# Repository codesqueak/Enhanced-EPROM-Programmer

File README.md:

# Enhanced EPROM-Programmer Version 2.7

2708 / 2716 Enhanced EPROM Programmer

## Introduction

This card has been designed to be a functional replacement for the Bits & PCs Nascom EPROM Programmer.  It is fully compatible with the existing software.

The card is a completely new implementation of the design with a number of improvements over the original:

* Single power source requirement (+5V only)
* Completely new track layout
* All components are readily available from commercial component suppliers (..and eBay!)
* Single power switch,  EPROM selection via standard 12 PIN DIL socket mounted switch
* LED power indicator
* Power test points
* Adjustable 25V feed for 2708's

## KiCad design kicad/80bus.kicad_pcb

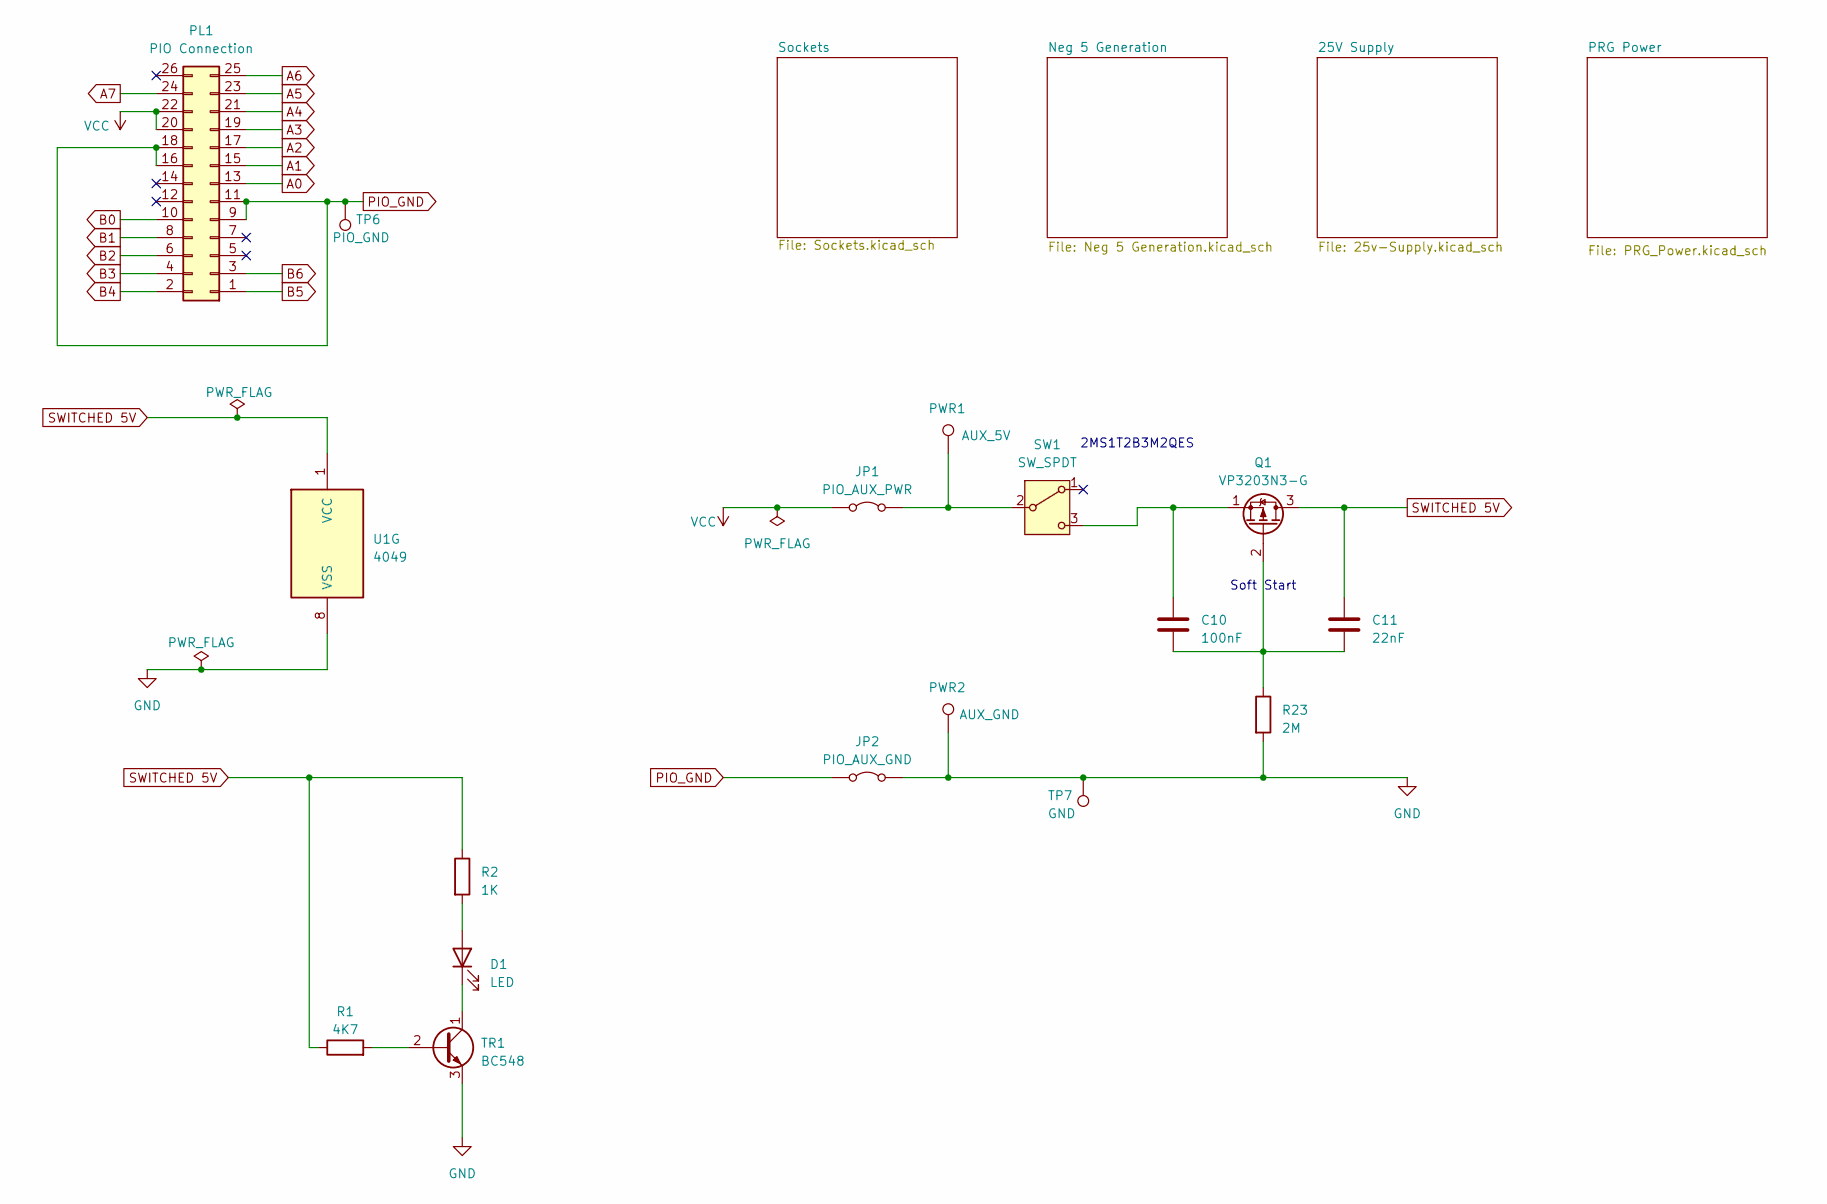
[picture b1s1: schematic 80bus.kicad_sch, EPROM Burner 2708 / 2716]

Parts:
C10: 100nF; C_Disc_D5.0mm_W2.5mm_P5.00mm
C11: 22nF; C_Disc_D5.0mm_W2.5mm_P5.00mm
D1: LED; LED_D3.0mm
JP1: PIO_AUX_PWR; PinHeader_1x02_P2.54mm_Vertical
JP2: PIO_AUX_GND; PinHeader_1x02_P2.54mm_Vertical
PL1: PIO Connection; PinHeader_2x13_P2.54mm_Vertical
PWR1: AUX_5V; TestPoint_THTPad_4.0x4.0mm_Drill2.0mm
PWR2: AUX_GND; TestPoint_THTPad_4.0x4.0mm_Drill2.0mm
Q1: VP3203N3-G; TO-92L_Inline
R1: 4K7; R_Axial_DIN0309_L9.0mm_D3.2mm_P12.70mm_Horizontal
R2: 1K; R_Axial_DIN0309_L9.0mm_D3.2mm_P12.70mm_Horizontal
R23: 2M; R_Axial_DIN0309_L9.0mm_D3.2mm_P12.70mm_Horizontal
SW1: SW_SPDT; PinHeader_1x03_P2.54mm_Vertical
TP6: PIO_GND; TestPoint_THTPad_2.0x2.0mm_Drill1.0mm
TP7: GND; TestPoint_THTPad_2.0x2.0mm_Drill1.0mm
TR1: BC548; TO-92_Inline_Wide
U1: 4049; DIP-16_W7.62mm_Socket

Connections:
A0: PL1.13; also elsewhere on the board
A1: PL1.15; also elsewhere on the board
A2: PL1.17; also elsewhere on the board
A3: PL1.19; also elsewhere on the board
A4: PL1.21; also elsewhere on the board
A5: PL1.23; also elsewhere on the board
A6: PL1.25; also elsewhere on the board
A7: PL1.24; also elsewhere on the board
B0: PL1.10; also elsewhere on the board
B1: PL1.8; also elsewhere on the board
B2: PL1.6; also elsewhere on the board
B3: PL1.4; also elsewhere on the board
B4: PL1.2; also elsewhere on the board
B5: PL1.1; also elsewhere on the board
B6: PL1.3; also elsewhere on the board
GND: JP2.1 (A), PWR2.1, R23.2, TP7.1, TR1.3 (E), U1.8 (VSS); also elsewhere on the board
unnamed: D1.2 (A), R2.2
unnamed: D1.1 (K), TR1.1 (C)
unnamed: JP1.1 (A), PWR1.1, SW1.2 (B)
unnamed: C10.2, C11.2, Q1.2 (G), R23.1
unnamed: C10.1, Q1.1 (S), SW1.3 (C)
unnamed: R1.2, TR1.2 (B)
PIO_GND: JP2.2 (B), PL1.9, PL1.11, PL1.16, PL1.18, TP6.1
SWITCHED 5V: C11.1, Q1.3 (D), R1.1, R2.1, U1.1 (VCC); also elsewhere on the board
VCC: JP1.2 (B), PL1.20, PL1.22

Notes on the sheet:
Soft Start
2MS1T2B3M2QES

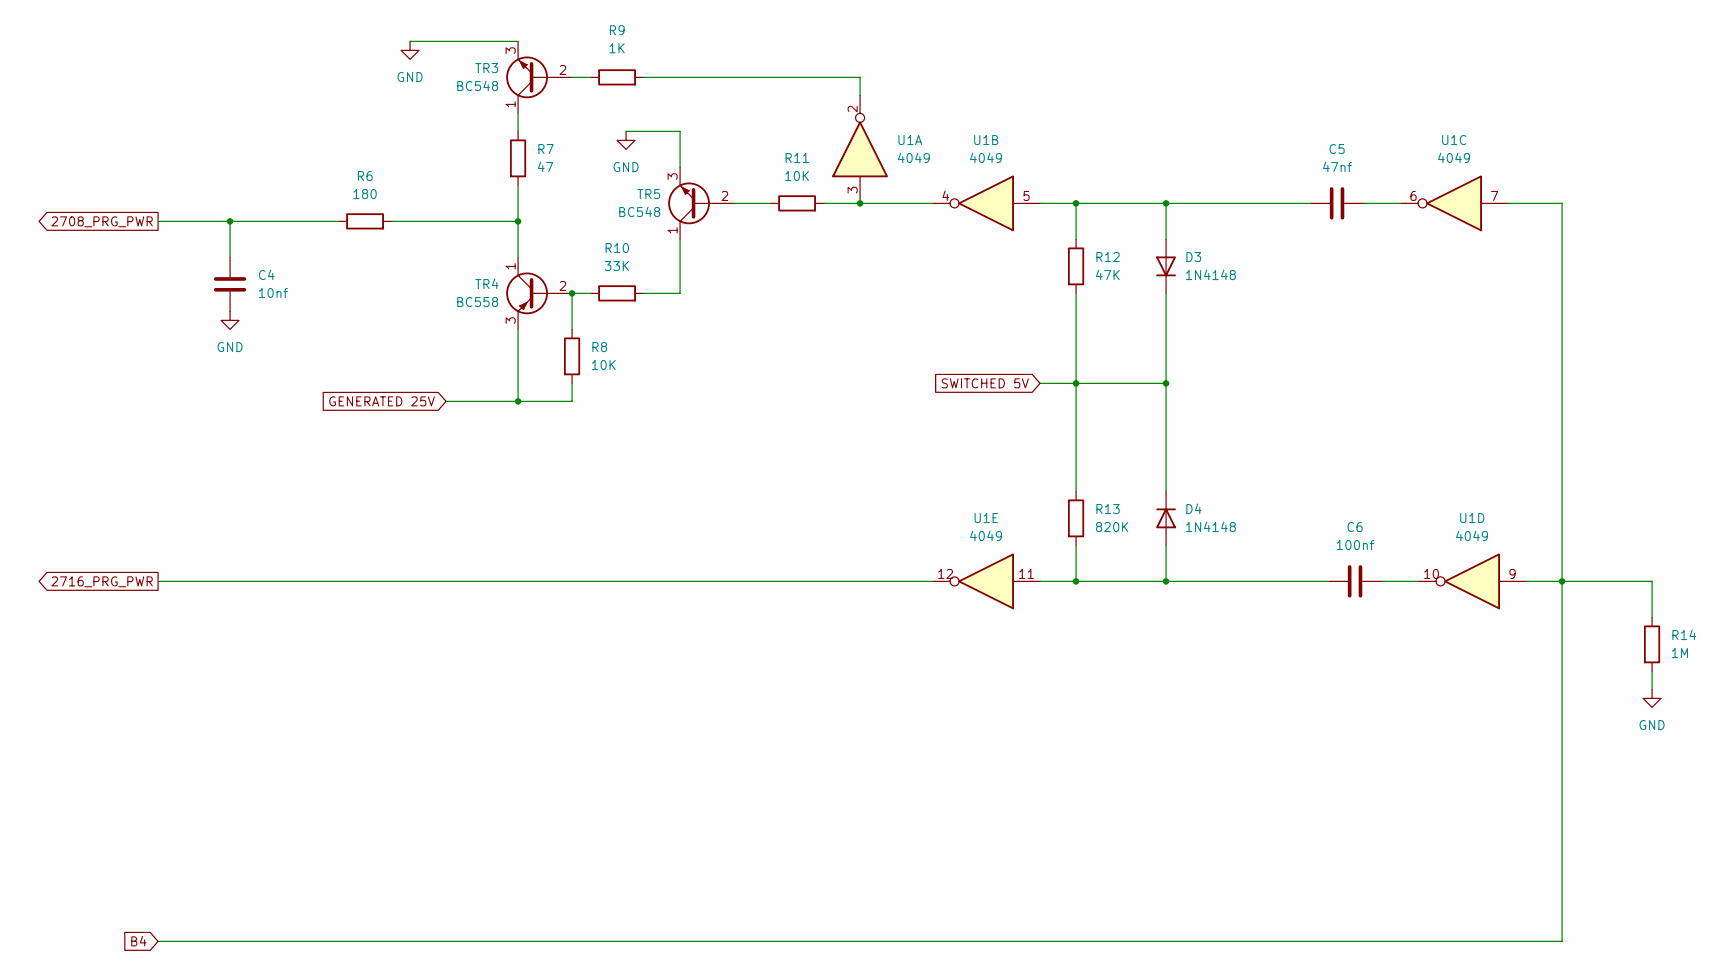
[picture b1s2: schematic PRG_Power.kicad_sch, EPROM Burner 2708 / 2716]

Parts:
C4: 10nf; C_Disc_D5.0mm_W2.5mm_P5.00mm
C5: 47nf; C_Disc_D5.0mm_W2.5mm_P5.00mm
C6: 100nf; C_Disc_D5.0mm_W2.5mm_P5.00mm
D3, D4: 1N4148; D_DO-41_SOD81_P10.16mm_Horizontal
R6: 180; R_Axial_DIN0309_L9.0mm_D3.2mm_P12.70mm_Horizontal
R7: 47; R_Axial_DIN0309_L9.0mm_D3.2mm_P12.70mm_Horizontal
R8, R11: 10K; R_Axial_DIN0309_L9.0mm_D3.2mm_P12.70mm_Horizontal
R9: 1K; R_Axial_DIN0309_L9.0mm_D3.2mm_P12.70mm_Horizontal
R10: 33K; R_Axial_DIN0309_L9.0mm_D3.2mm_P12.70mm_Horizontal
R12: 47K; R_Axial_DIN0309_L9.0mm_D3.2mm_P12.70mm_Horizontal
R13: 820K; R_Axial_DIN0309_L9.0mm_D3.2mm_P12.70mm_Horizontal
R14: 1M; R_Axial_DIN0309_L9.0mm_D3.2mm_P12.70mm_Horizontal
TR3, TR5: BC548; TO-92_Inline_Wide
TR4: BC558; TO-92_Inline_Wide
U1: 4049; DIP-16_W7.62mm_Socket

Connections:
2708_PRG_PWR: C4.1, R6.1; also elsewhere on the board
2716_PRG_PWR: U1.12; also elsewhere on the board
B4: R14.1, U1.7, U1.9; also elsewhere on the board
GENERATED 25V: R8.2, TR4.3 (E); also elsewhere on the board
GND: C4.2, R14.2, TR3.3 (E), TR5.3 (E); also elsewhere on the board
unnamed: C5.2, U1.6
unnamed: C6.1, U1.10
unnamed: C5.1, D3.2 (A), R12.1, U1.5
unnamed: C6.2, D4.2 (A), R13.2, U1.11
unnamed: R9.2, U1.2
unnamed: R11.2, U1.3, U1.4
unnamed: R9.1, TR3.2 (B)
unnamed: R7.1, TR3.1 (C)
unnamed: R8.1, R10.1, TR4.2 (B)
unnamed: R6.2, R7.2, TR4.1 (C)
unnamed: R11.1, TR5.2 (B)
unnamed: R10.2, TR5.1 (C)
SWITCHED 5V: D3.1 (K), D4.1 (K), R12.2, R13.1; also elsewhere on the board

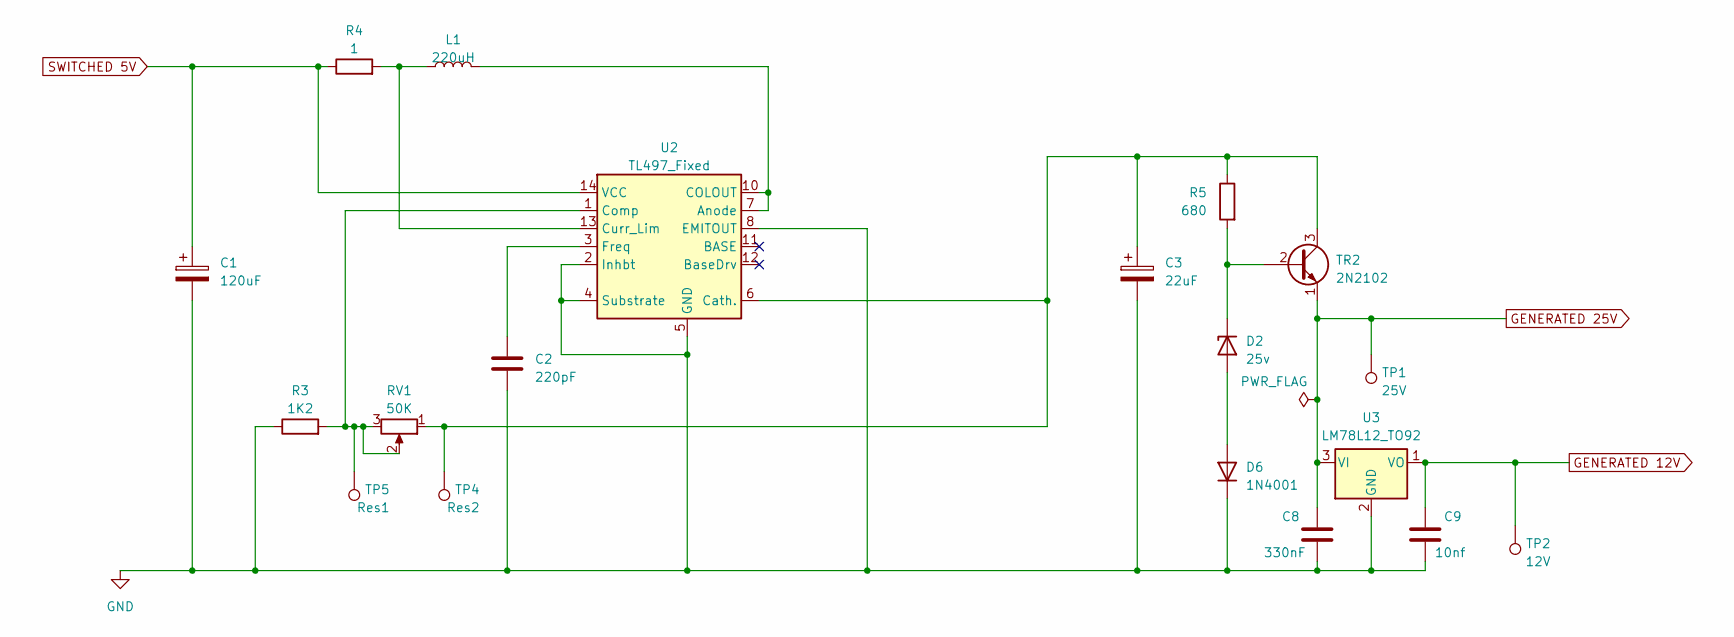
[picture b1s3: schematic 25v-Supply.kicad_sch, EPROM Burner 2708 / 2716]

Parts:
C1: 120uF; CP_Radial_D10.0mm_P5.00mm
C2: 220pF; C_Disc_D5.0mm_W2.5mm_P5.00mm
C3: 22uF; CP_Radial_D5.0mm_P2.50mm
C8: 330nF; C_Disc_D5.0mm_W2.5mm_P5.00mm
C9: 10nf; C_Disc_D5.0mm_W2.5mm_P5.00mm
D2: 25v; D_DO-41_SOD81_P12.70mm_Horizontal
D6: 1N4001; D_DO-41_SOD81_P10.16mm_Horizontal
L1: 220uH; L_Radial_D7.8mm_P5.00mm_Fastron_07HCP
R3: 1K2; R_Axial_DIN0309_L9.0mm_D3.2mm_P12.70mm_Horizontal
R4: 1; R_Axial_DIN0309_L9.0mm_D3.2mm_P12.70mm_Horizontal
R5: 680; R_Axial_DIN0309_L9.0mm_D3.2mm_P12.70mm_Horizontal
RV1: 50K; Potentiometer_Vishay_43_Horizontal
TP1: 25V; TestPoint_THTPad_2.0x2.0mm_Drill1.0mm
TP2: 12V; TestPoint_THTPad_2.0x2.0mm_Drill1.0mm
TP4: Res2; TestPoint_THTPad_2.0x2.0mm_Drill1.0mm
TP5: Res1; TestPoint_THTPad_2.0x2.0mm_Drill1.0mm
TR2: 2N2102; TO-39-3
U2: TL497_Fixed; DIP-14_W7.62mm_Socket
U3: LM78L12_TO92; TO-92_Inline

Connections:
GENERATED 12V: C9.1, TP2.1, U3.1 (VO); also elsewhere on the board
GENERATED 25V: C8.1, TP1.1, TR2.1 (E), U3.3 (VI); also elsewhere on the board
GND: C1.2, C2.2, C3.2, C8.2, C9.2, D6.1 (K), R3.1, U2.2 (Inhbt), U2.4 (Substrate), U2.5 (GND), U2.8 (EMITOUT), U3.2 (GND); also elsewhere on the board
unnamed: D2.2 (A), D6.2 (A)
unnamed: D2.1 (K), R5.2, TR2.2 (B)
unnamed: C3.1, R5.1, RV1.1, TP4.1, TR2.3 (C), U2.6 (Cath.)
unnamed: L1.2, U2.7 (Anode), U2.10 (COLOUT)
unnamed: R3.2, RV1.2, RV1.3, TP5.1, U2.1 (Comp)
unnamed: L1.1, R4.2, U2.13 (Curr_Lim)
unnamed: C2.1, U2.3 (Freq)
SWITCHED 5V: C1.1, R4.1, U2.14 (VCC); also elsewhere on the board

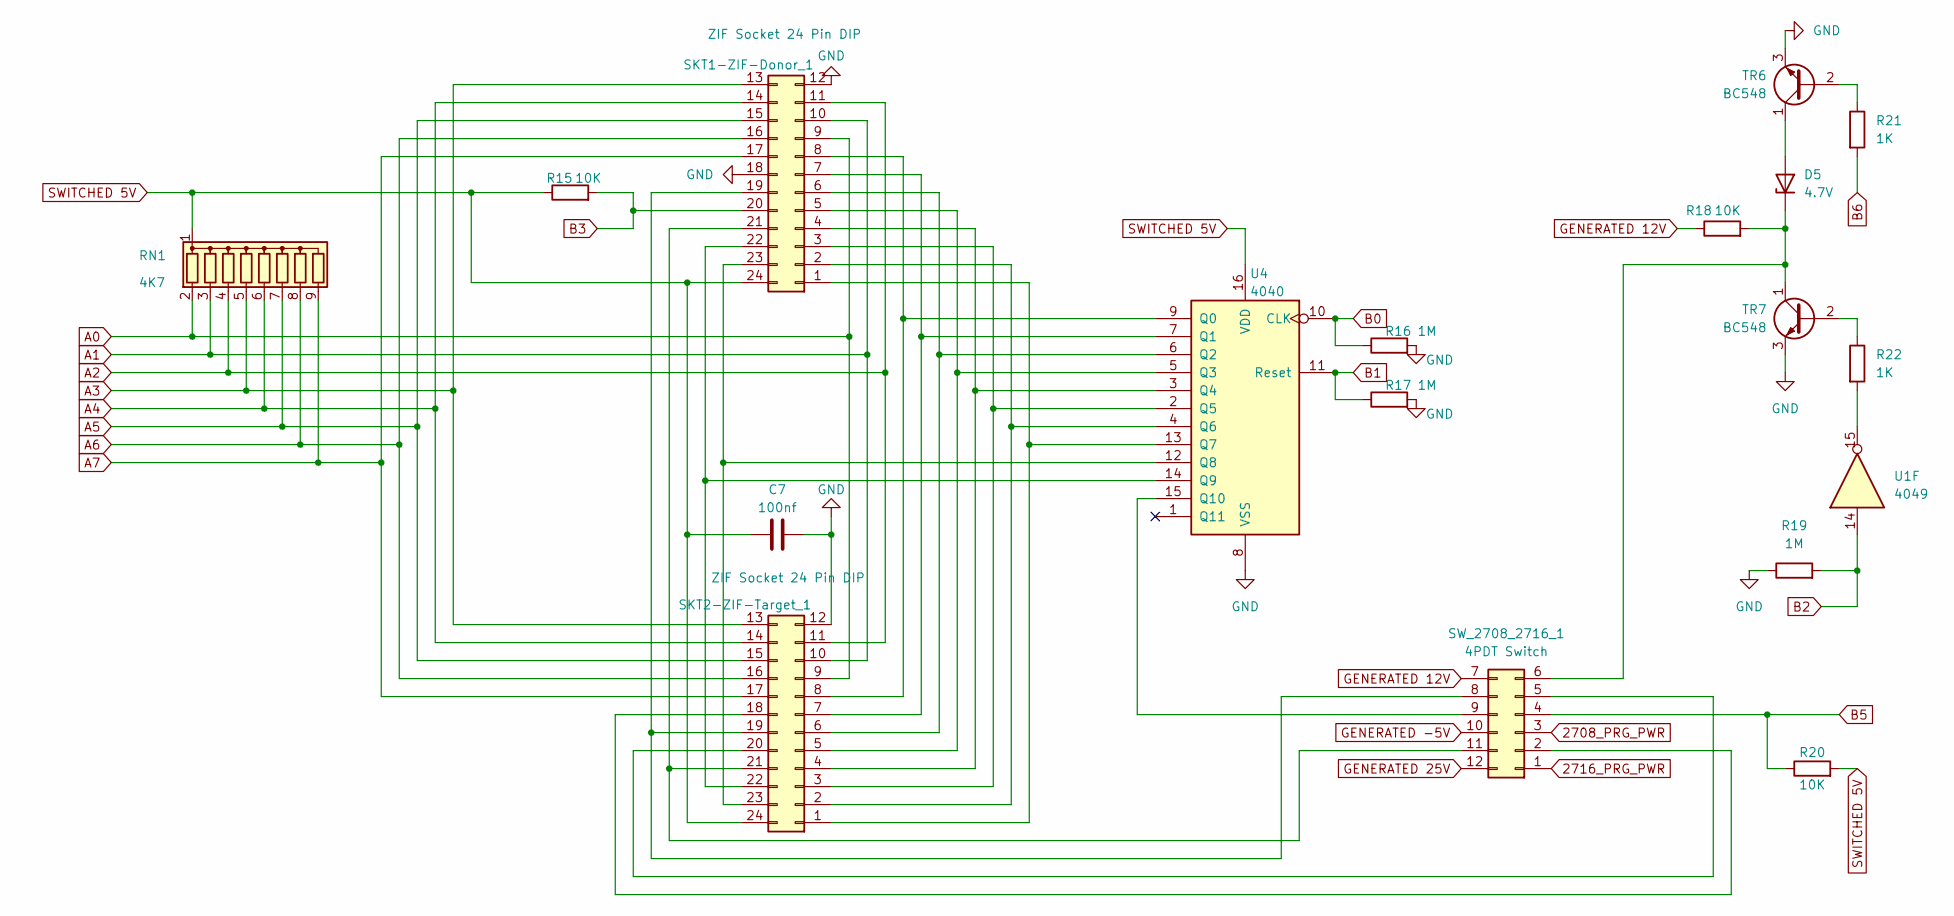
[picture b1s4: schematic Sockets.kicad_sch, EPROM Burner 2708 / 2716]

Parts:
C7: 100nf; C_Disc_D5.0mm_W2.5mm_P5.00mm
D5: 4.7V; D_DO-41_SOD81_P12.70mm_Horizontal
R15, R18, R20: 10K; R_Axial_DIN0309_L9.0mm_D3.2mm_P12.70mm_Horizontal
R16, R17, R19: 1M; R_Axial_DIN0309_L9.0mm_D3.2mm_P12.70mm_Horizontal
R21, R22: 1K; R_Axial_DIN0309_L9.0mm_D3.2mm_P12.70mm_Horizontal
RN1: 4K7; R_Array_SIP9
SKT1-ZIF-Donor_1, SKT2-ZIF-Target_1: ZIF Socket 24 Pin DIP; DIP-24_W15.24mm_Socket
SW_2708_2716_1: 4PDT Switch; DIP-12_W7.62mm_Socket
TR6, TR7: BC548; TO-92_Inline_Wide
U1: 4049; DIP-16_W7.62mm_Socket
U4: 4040; DIP-16_W7.62mm_Socket

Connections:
2708_PRG_PWR: SW_2708_2716_1.3; also elsewhere on the board
2716_PRG_PWR: SW_2708_2716_1.1; also elsewhere on the board
A0: RN1.2 (R1), SKT1-ZIF-Donor_1.9, SKT2-ZIF-Target_1.9; also elsewhere on the board
A1: RN1.3 (R2), SKT1-ZIF-Donor_1.10, SKT2-ZIF-Target_1.10; also elsewhere on the board
A2: RN1.4 (R3), SKT1-ZIF-Donor_1.11, SKT2-ZIF-Target_1.11; also elsewhere on the board
A3: RN1.5 (R4), SKT1-ZIF-Donor_1.13, SKT2-ZIF-Target_1.13; also elsewhere on the board
A4: RN1.6 (R5), SKT1-ZIF-Donor_1.14, SKT2-ZIF-Target_1.14; also elsewhere on the board
A5: RN1.7 (R6), SKT1-ZIF-Donor_1.15, SKT2-ZIF-Target_1.15; also elsewhere on the board
A6: RN1.8 (R7), SKT1-ZIF-Donor_1.16, SKT2-ZIF-Target_1.16; also elsewhere on the board
A7: RN1.9 (R8), SKT1-ZIF-Donor_1.17, SKT2-ZIF-Target_1.17; also elsewhere on the board
B0: R16.1, U4.10 (CLK); also elsewhere on the board
B1: R17.1, U4.11 (Reset); also elsewhere on the board
B2: R19.2, U1.14; also elsewhere on the board
B3: R15.2, SKT1-ZIF-Donor_1.20; also elsewhere on the board
B5: R20.1, SW_2708_2716_1.4; also elsewhere on the board
B6: R21.2; also elsewhere on the board
GENERATED 12V: R18.1, SW_2708_2716_1.7; also elsewhere on the board
GENERATED 25V: SW_2708_2716_1.12; also elsewhere on the board
GENERATED -5V: SW_2708_2716_1.10; also elsewhere on the board
GND: C7.2, R16.2, R17.2, R19.1, SKT1-ZIF-Donor_1.12, SKT1-ZIF-Donor_1.18, SKT2-ZIF-Target_1.12, TR6.3 (E), TR7.3 (E), U4.8 (VSS); also elsewhere on the board
unnamed: D5.2 (A), TR6.1 (C)
unnamed: D5.1 (K), R18.2, SW_2708_2716_1.6, TR7.1 (C)
unnamed: R22.2, U1.15
unnamed: SKT1-ZIF-Donor_1.1, SKT2-ZIF-Target_1.1, U4.13 (Q7)
unnamed: SKT1-ZIF-Donor_1.2, SKT2-ZIF-Target_1.2, U4.4 (Q6)
unnamed: SKT1-ZIF-Donor_1.3, SKT2-ZIF-Target_1.3, U4.2 (Q5)
unnamed: SKT1-ZIF-Donor_1.4, SKT2-ZIF-Target_1.4, U4.3 (Q4)
unnamed: SKT1-ZIF-Donor_1.5, SKT2-ZIF-Target_1.5, U4.5 (Q3)
unnamed: SKT1-ZIF-Donor_1.6, SKT2-ZIF-Target_1.6, U4.6 (Q2)
unnamed: SKT1-ZIF-Donor_1.7, SKT2-ZIF-Target_1.7, U4.7 (Q1)
unnamed: SKT1-ZIF-Donor_1.8, SKT2-ZIF-Target_1.8, U4.9 (Q0)
unnamed: SKT1-ZIF-Donor_1.19, SKT2-ZIF-Target_1.19, SW_2708_2716_1.8
unnamed: SKT1-ZIF-Donor_1.21, SKT2-ZIF-Target_1.21, SW_2708_2716_1.11
unnamed: SKT1-ZIF-Donor_1.22, SKT2-ZIF-Target_1.22, U4.14 (Q9)
unnamed: SKT1-ZIF-Donor_1.23, SKT2-ZIF-Target_1.23, U4.12 (Q8)
unnamed: SKT2-ZIF-Target_1.18, SW_2708_2716_1.2
unnamed: SKT2-ZIF-Target_1.20, SW_2708_2716_1.5
unnamed: SW_2708_2716_1.9, U4.15 (Q10)
unnamed: R21.1, TR6.2 (B)
unnamed: R22.1, TR7.2 (B)
SWITCHED 5V: C7.1, R15.1, R20.2, RN1.1 (common), SKT1-ZIF-Donor_1.24, SKT2-ZIF-Target_1.24, U4.16 (VDD); also elsewhere on the board

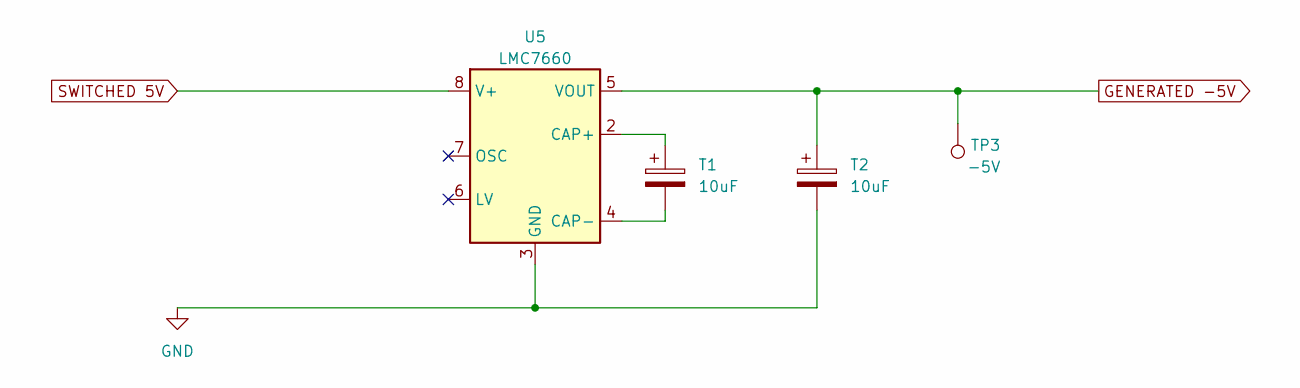
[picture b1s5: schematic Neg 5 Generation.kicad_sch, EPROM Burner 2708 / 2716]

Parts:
T1, T2: 10uF; C_Disc_D7.5mm_W5.0mm_P5.00mm
TP3: -5V; TestPoint_THTPad_2.0x2.0mm_Drill1.0mm
U5: LMC7660; DIP-8_W7.62mm_Socket

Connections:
GENERATED -5V: T2.1, TP3.1, U5.5 (VOUT); also elsewhere on the board
GND: T2.2, U5.3 (GND); also elsewhere on the board
unnamed: T1.1, U5.2 (CAP+)
unnamed: T1.2, U5.4 (CAP-)
SWITCHED 5V: U5.8 (V+); also elsewhere on the board

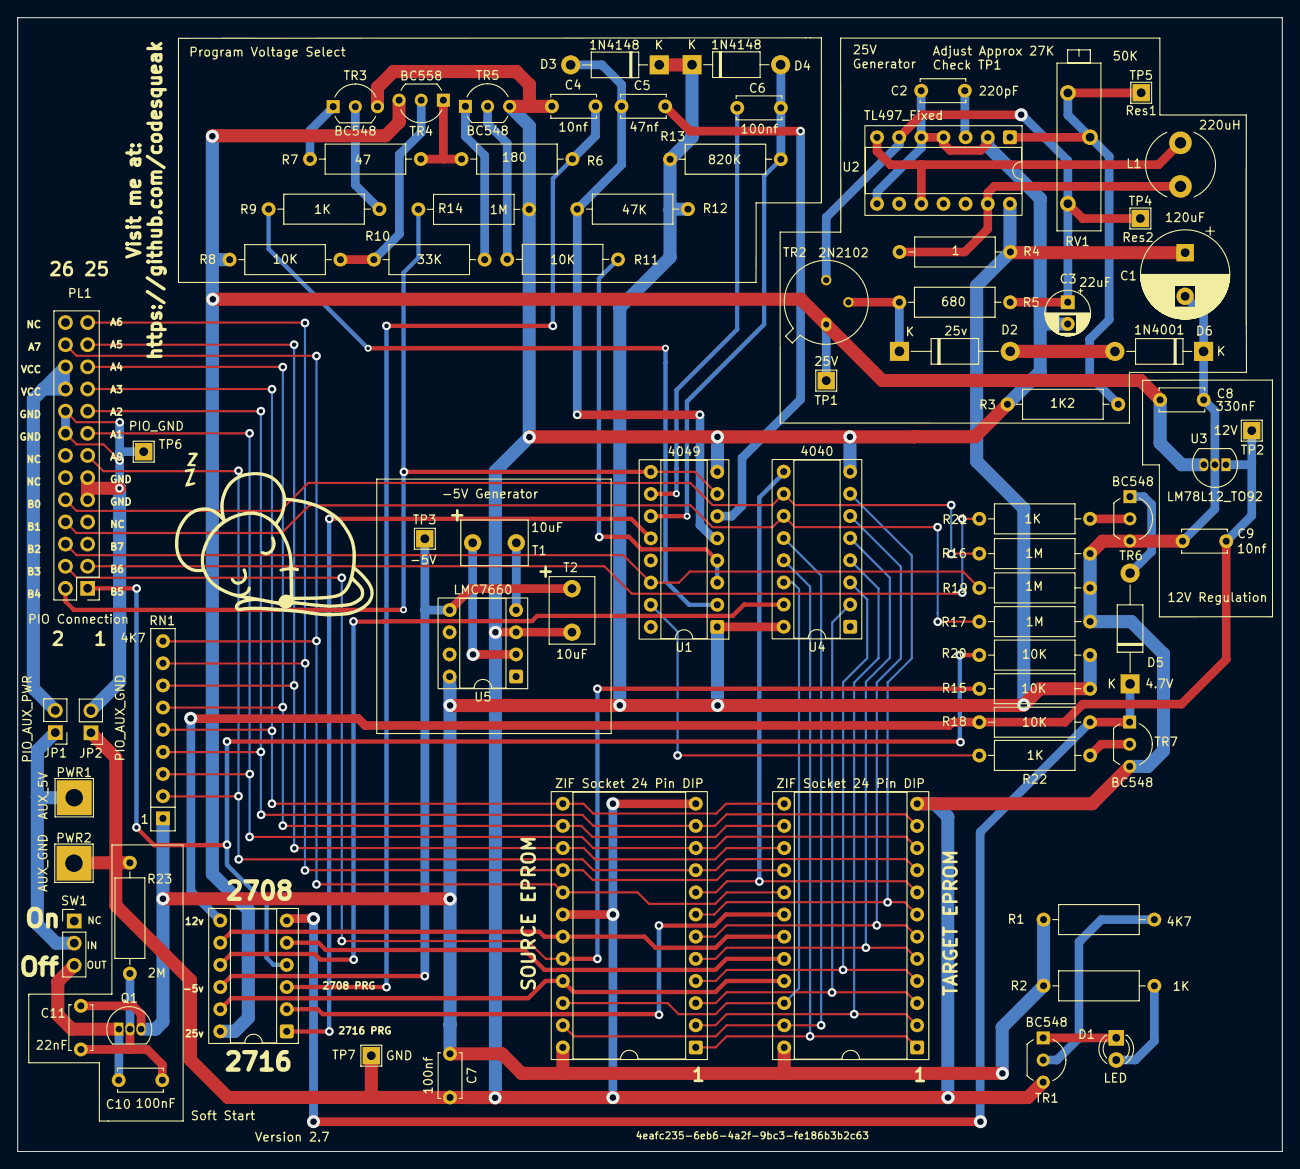
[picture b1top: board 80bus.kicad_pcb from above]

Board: 2 copper layers, 145.0 x 130.0 mm, 76 parts (1 on the bottom side), 71 nets.

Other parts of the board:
G1: LOGO; sleepymouse
G001: LOGO; qr-code

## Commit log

2023-06-18 Initial code drop
2023-06-20 Add image
2023-06-20 Silkscreen tidy
2023-07-09 Add aux power feeds
2023-07-09 Minor doc change
2023-08-14 Add soft start
2023-09-01 Minor error - wrong resistor value as R13
2023-10-07 Updated docs
2024-10-06 Kicad 8, updated docs
2025-04-16 Update docs
2025-04-23 Update footprints
